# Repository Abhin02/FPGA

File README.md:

# FPGA Interfacing

This project is a set of all the files and documentation of the FPGA project work that was carried out in WEL Laboratory - IIT Bombay during Summer 2016.

## Aim
* To build and program a circuit that uses a CPLD controller to divide computations between two FPGA chips.
* To program Altera CPLD chip using a microcontroller which emulates the Altera USB Blaster. This would allow direct programming from Quartus II without the hassles of external hardware requirements, UrJTAG and the need to create Serial Vector files.

## Circuit Designs

We have added the Eagle files for the Krypton Board, an Altera Max V based development board that was designed earlier by WEL Laboratory. We used this board for testing and building the circuit. The files can be found under [eagle/Krypton/](eagle/Krypton/). There are two eagle files, a daughter card for housing the Max V CPLD IC and a main board for the development board peripherals, such as LEDs and switches.

The board we worked on has been designed under [eagle/main_circuit.sch](eagle/main_circuit.sch) and [eagle/main_circuit.sch](eagle/main_circuit.sch)

A detailed documentation of the project can be found in [report.pdf](report.pdf)

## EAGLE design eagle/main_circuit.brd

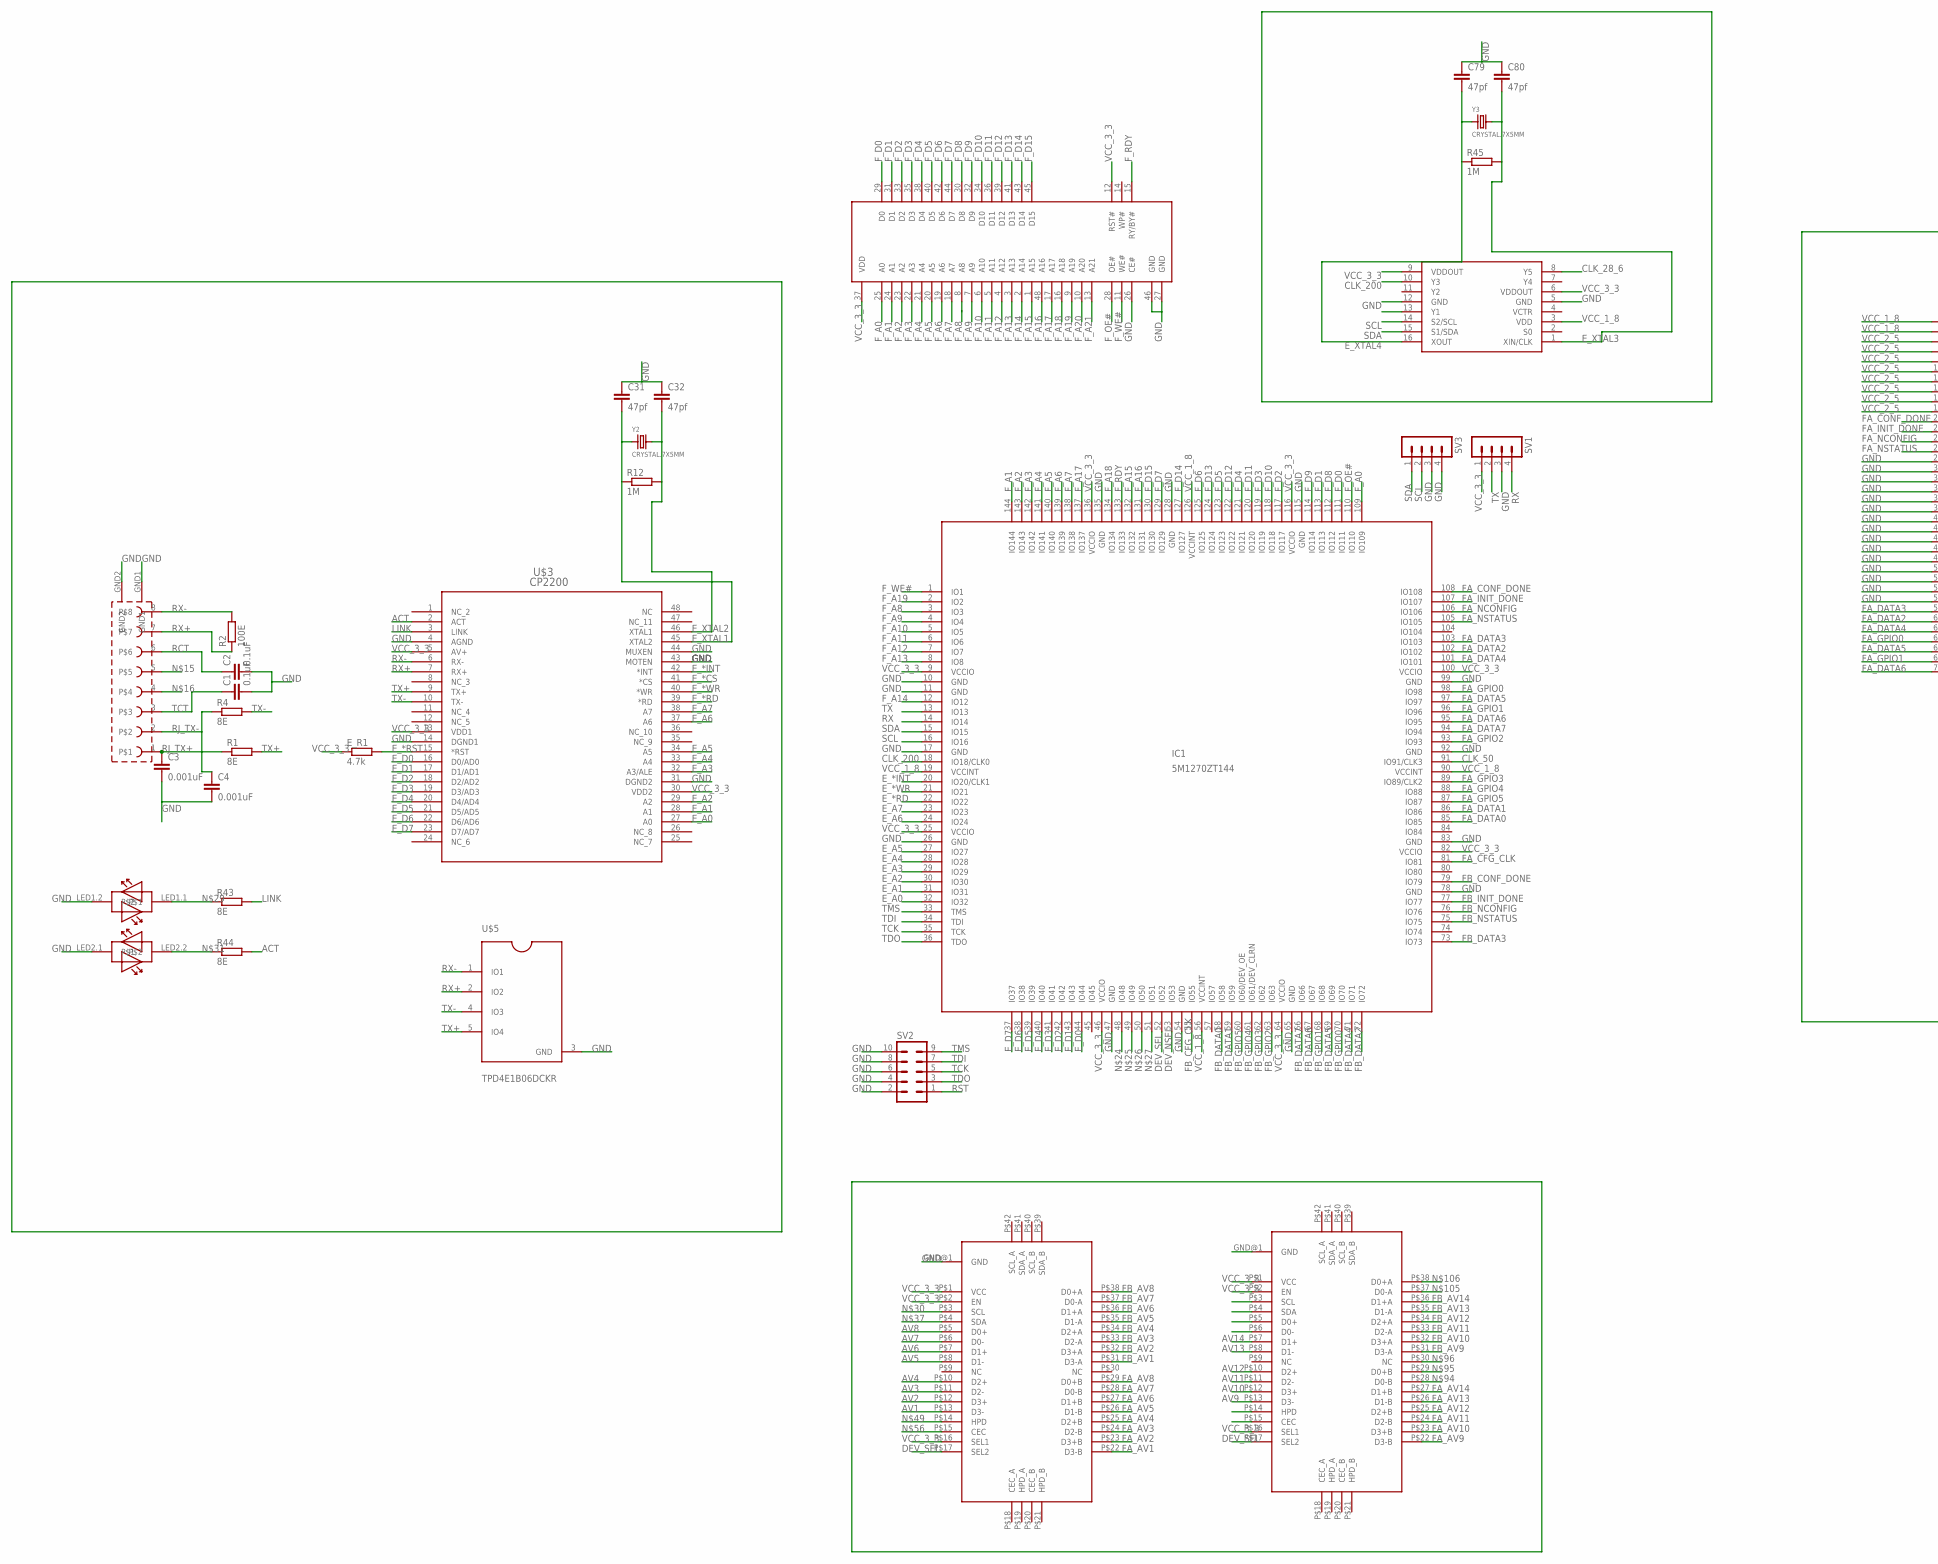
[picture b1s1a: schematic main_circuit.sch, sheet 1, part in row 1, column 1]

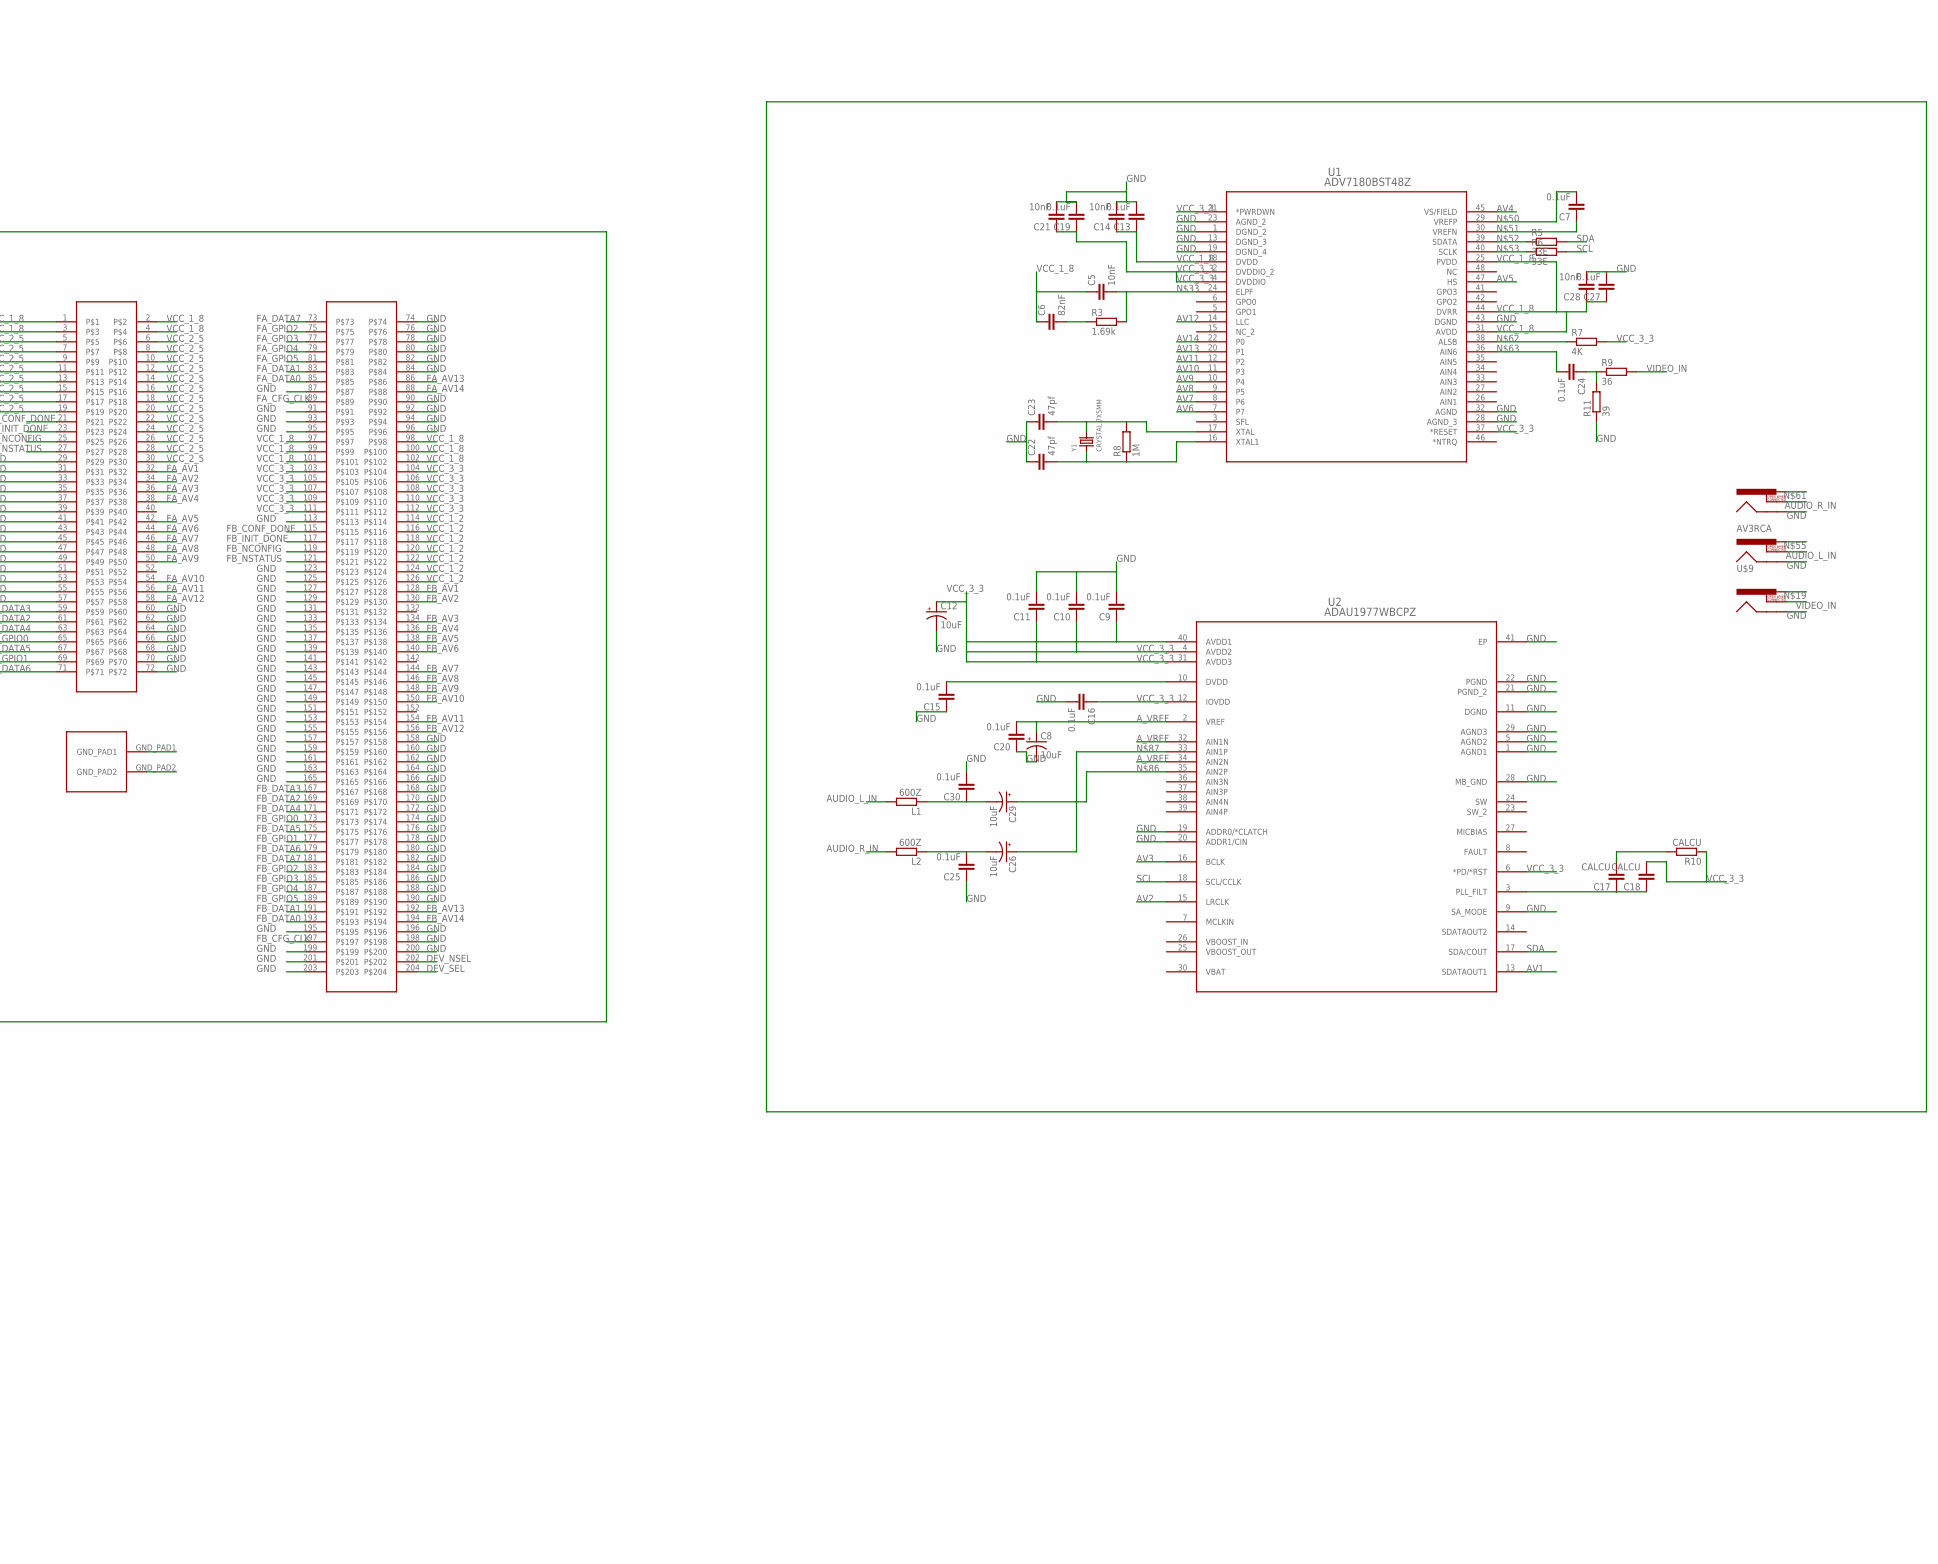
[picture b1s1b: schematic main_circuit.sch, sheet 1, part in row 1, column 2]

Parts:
C1, C2: 0.1uF; C0402
C3, C4: 0.001uF; C0402
C5, C14, C21, C28: 10nF; C0603
C6: 82nF; C0603
C7, C9, C10, C11, C13, C15, C16, C19, C20, C24, C25, C27, C30: 0.1uF; C0603
C8, C12, C26, C29: 10uF; E2,5-6E
C17, C18: CALCU; C0603
C22, C23, C31, C32, C79, C80: 47pf; C0603
E_R1: 4.7k; R0603
GND: TS3DV642; R-PWQFN-N42
IC1: 5M1270ZT144; TQFP144
L1, L2: 600Z; R0603
R1, R4, R43, R44: 8E; R0402
R2: 100E; R0402
R3: 1.69k; R0603
R5, R6: 33E; R0603
R7: 4K; R0603
R8, R12, R45: 1M; R0603
R9: 36; R0603
R10: CALCU; R0603
R11: 39; R0603
SV1, SV3: MA04-1
SV2: MA05-2
U1: ADV7180BST48Z; ST_48
U2: ADAU1977WBCPZ; CP_40_14
U$1: SST39VF64; TSOP48
U$2: CDCE925; R-PDSO-G16
U$3: CP2200; QFP48-7X7-0P5MM
U$4: SODIMM; SODIMM_DDR3_CONN
U$5: TPD4E1B06DCKR; SC70-6
U$6: MAGJACK
U$8: TS3DV642; R-PWQFN-N42
U$9: AV3RCA
Y1, Y2, Y3: CRYSTAL.7X5MM; 7X5MM

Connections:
ACT: R44.2, U$3.2 (ACT)
AUDIO_L_IN: L1.2, U$9.SWITCH
AUDIO_R_IN: L2.2, U$9.SWITCH1
AV1: GND.P$13 (D3-), U2.13 (SDATAOUT1)
AV2: GND.P$12 (D3+), U2.15 (LRCLK)
AV3: GND.P$11 (D2-), U2.16 (BCLK)
AV4: GND.P$10 (D2+), U1.45 (VS/FIELD)
AV5: GND.P$8 (D1-), U1.47 (HS)
AV6: GND.P$7 (D1+), U1.7
AV7: GND.P$6 (D0-), U1.8 (P6)
AV8: GND.P$5 (D0+), U1.9 (P5)
AV9: U1.10 (P4), U$8.P$13 (D3-)
AV10: U1.11 (P3), U$8.P$12 (D3+)
AV11: U1.12 (P2), U$8.P$11 (D2-)
AV12: U1.14 (LLC), U$8.P$10 (D2+)
AV13: U1.20 (P1), U$8.P$8 (D1-)
AV14: U1.22 (P0), U$8.P$7 (D1+)
A_VREF: C8.+, C20.2, U2.2 (VREF), U2.32 (AIN1N), U2.34 (AIN2N)
CLK_28_6: U$2.8 (Y5)
CLK_50: IC1.91 (IO91/CLK3), U$2.13 (Y1)
CLK_200: IC1.18 (IO18/CLK0), U$2.10 (Y3)
DEV_NSEL: IC1.53 (IO53), U$4.202
DEV_SEL: GND.P$17 (SEL2), IC1.52 (IO52), U$4.204, U$8.P$17 (SEL2)
E_*CS: U$3.41 (*CS)
E_*INT: IC1.20 (IO20/CLK1), U$3.42 (*INT)
E_*RD: IC1.22 (IO22), U$3.39 (*RD)
E_*RST: E_R1.2, U$3.15 (*RST)
E_*WR: IC1.21 (IO21), U$3.40 (*WR)
E_A0: IC1.32 (IO32), U$3.27 (A0)
E_A1: IC1.31 (IO31), U$3.28 (A1)
E_A2: IC1.30 (IO30), U$3.29 (A2)
E_A3: IC1.29 (IO29), U$3.32 (A3/ALE)
E_A4: IC1.28 (IO28), U$3.33 (A4)
E_A5: IC1.27 (IO27), U$3.34 (A5)
E_A6: IC1.24 (IO24), U$3.37 (A6)
E_A7: IC1.23 (IO23), U$3.38 (A7)
E_D0: IC1.44 (IO44), U$3.16 (D0/AD0)
E_D1: IC1.43 (IO43), U$3.17 (D1/AD1)
E_D2: IC1.42 (IO42), U$3.18 (D2/AD2)
E_D3: IC1.41 (IO41), U$3.19 (D3/AD3)
E_D4: IC1.40 (IO40), U$3.20 (D4/AD4)
E_D5: IC1.39 (IO39), U$3.21 (D5/AD5)
E_D6: IC1.38 (IO38), U$3.22 (D6/AD6)
E_D7: IC1.37 (IO37), U$3.23 (D7/AD7)
E_XTAL1: C31.2, R12.1, U$3.45 (XTAL2), Y2.1
E_XTAL2: C32.2, R12.2, U$3.46 (XTAL1), Y2.3 (2)
E_XTAL3: C80.2, R45.2, U$2.1 (XIN/CLK), Y3.3 (2)
E_XTAL4: C79.2, R45.1, U$2.16 (XOUT), Y3.1
FA_AV1: GND.P$22 (D3-B), U$4.32
FA_AV2: GND.P$23 (D3+B), U$4.34
FA_AV3: GND.P$24 (D2-B), U$4.36
FA_AV4: GND.P$25 (D2+B), U$4.38
FA_AV5: GND.P$26 (D1-B), U$4.42
FA_AV6: GND.P$27 (D1+B), U$4.44
FA_AV7: GND.P$28 (D0-B), U$4.46
FA_AV8: GND.P$29 (D0+B), U$4.48
FA_AV9: U$4.50, U$8.P$22 (D3-B)
FA_AV10: U$4.54, U$8.P$23 (D3+B)
FA_AV11: U$4.56, U$8.P$24 (D2-B)
FA_AV12: U$4.58, U$8.P$25 (D2+B)
FA_AV13: U$4.86, U$8.P$26 (D1-B)
FA_AV14: U$4.88, U$8.P$27 (D1+B)
FA_CFG_CLK: IC1.81 (IO81), U$4.89
FA_CONF_DONE: IC1.108 (IO108), U$4.21
FA_DATA0: IC1.85 (IO85), U$4.85
FA_DATA1: IC1.86 (IO86), U$4.83
FA_DATA2: IC1.102 (IO102), U$4.61
FA_DATA3: IC1.103 (IO103), U$4.59
FA_DATA4: IC1.101 (IO101), U$4.63
FA_DATA5: IC1.97 (IO97), U$4.67
FA_DATA6: IC1.95 (IO95), U$4.71
FA_DATA7: IC1.94 (IO94), U$4.73
FA_GPIO0: IC1.98 (IO98), U$4.65
FA_GPIO1: IC1.96 (IO96), U$4.69
FA_GPIO2: IC1.93 (IO93), U$4.75
FA_GPIO3: IC1.89 (IO89/CLK2), U$4.77
FA_GPIO4: IC1.88 (IO88), U$4.79
FA_GPIO5: IC1.87 (IO87), U$4.81
FA_INIT_DONE: IC1.107 (IO107), U$4.23
FA_NCONFIG: IC1.106 (IO106), U$4.25
FA_NSTATUS: IC1.105 (IO105), U$4.27
FB_AV1: GND.P$31 (D3-A), U$4.128
FB_AV2: GND.P$32 (D3+A), U$4.130
FB_AV3: GND.P$33 (D2-A), U$4.134
FB_AV4: GND.P$34 (D2+A), U$4.136
FB_AV5: GND.P$35 (D1-A), U$4.138
FB_AV6: GND.P$36 (D1+A), U$4.140
FB_AV7: GND.P$37 (D0-A), U$4.144
FB_AV8: GND.P$38 (D0+A), U$4.146
FB_AV9: U$4.148, U$8.P$31 (D3-A)
FB_AV10: U$4.150, U$8.P$32 (D3+A)
FB_AV11: U$4.154, U$8.P$33 (D2-A)
FB_AV12: U$4.156, U$8.P$34 (D2+A)
FB_AV13: U$4.192, U$8.P$35 (D1-A)
FB_AV14: U$4.194, U$8.P$36 (D1+A)
FB_CFG_CLK: IC1.55 (IO55), U$4.197
FB_CONF_DONE: IC1.79 (IO79), U$4.115
FB_DATA0: IC1.58 (IO58), U$4.193
FB_DATA1: IC1.59 (IO59), U$4.191
FB_DATA2: IC1.72 (IO72), U$4.169
FB_DATA3: IC1.73 (IO73), U$4.167
FB_DATA4: IC1.71 (IO71), U$4.171
FB_DATA5: IC1.69 (IO69), U$4.175
FB_DATA6: IC1.67 (IO67), U$4.179
FB_DATA7: IC1.66 (IO66), U$4.181
FB_GPIO0: IC1.70 (IO70), U$4.173
FB_GPIO1: IC1.68 (IO68), U$4.177
FB_GPIO2: IC1.63 (IO63), U$4.183
FB_GPIO3: IC1.62 (IO62), U$4.185
FB_GPIO4: IC1.61 (IO61/DEV_CLRN), U$4.187
FB_GPIO5: IC1.60 (IO60/DEV_OE), U$4.189
FB_INIT_DONE: IC1.77 (IO77), U$4.117
FB_NCONFIG: IC1.76 (IO76), U$4.119
FB_NSTATUS: IC1.75 (IO75), U$4.121
F_A0: IC1.109 (IO109), U$1.25 (A0)
F_A1: IC1.144 (IO144), U$1.24 (A1)
F_A2: IC1.143 (IO143), U$1.23 (A2)
F_A3: IC1.142 (IO142), U$1.22 (A3)
F_A4: IC1.141 (IO141), U$1.21 (A4)
F_A5: IC1.140 (IO140), U$1.20 (A5)
F_A6: IC1.139 (IO139), U$1.19 (A6)
F_A7: IC1.138 (IO138), U$1.18 (A7)
F_A8: IC1.3 (IO3), U$1.8 (A8)
F_A9: IC1.4 (IO4), U$1.7 (A9)
F_A10: IC1.5 (IO5), U$1.6 (A10)
F_A11: IC1.6 (IO6), U$1.5 (A11)
F_A12: IC1.7 (IO7), U$1.4 (A12)
F_A13: IC1.8 (IO8), U$1.3 (A13)
F_A14: IC1.12 (IO12), U$1.2 (A14)
F_A15: IC1.132 (IO132), U$1.1 (A15)
F_A16: IC1.131 (IO131), U$1.48 (A16)
F_A17: IC1.137 (IO137), U$1.17 (A17)
F_A18: IC1.134 (IO134), U$1.16 (A18)
F_A19: IC1.2 (IO2), U$1.9 (A19)
F_A20: U$1.10 (A20)
F_A21: U$1.13 (A21)
F_D0: IC1.111 (IO111), U$1.29 (D0)
F_D1: IC1.113 (IO113), U$1.31 (D1)
F_D2: IC1.117 (IO117), U$1.33 (D2)
F_D3: IC1.119 (IO119), U$1.35 (D3)
F_D4: IC1.121 (IO121), U$1.38 (D4)
F_D5: IC1.123 (IO123), U$1.40 (D5)
F_D6: IC1.125 (IO125), U$1.42 (D6)
F_D7: IC1.129 (IO129), U$1.44 (D7)
F_D8: IC1.112 (IO112), U$1.30 (D8)
F_D9: IC1.114 (IO114), U$1.32 (D9)
F_D10: IC1.118 (IO118), U$1.34 (D10)
F_D11: IC1.120 (IO120), U$1.36 (D11)
F_D12: IC1.122 (IO122), U$1.39 (D12)
F_D13: IC1.124 (IO124), U$1.41 (D13)
F_D14: IC1.127 (IO127), U$1.43 (D14)
F_D15: IC1.130 (IO130), U$1.45 (D15)
F_OE#: IC1.110 (IO110), U$1.28 (OE#)
F_RDY: IC1.133 (IO133), U$1.15 (RY/BY#)
F_WE#: IC1.1 (IO1), U$1.11 (WE#)
GND: C1.2, C2.2, C3.2, C4.2, C8.-, C9.2, C10.2, C11.2, C12.-, C13.2, C14.2, C15.1, C16.2, C19.2, C20.1, C21.2, C22.1, C23.1, C25.1, C27.2, C28.2, C30.2, C31.1, C32.1, C79.1, C80.1, GND.GND@1 (GND), IC1.10 (GND), IC1.11 (GND), IC1.17 (GND), IC1.26 (GND), IC1.47 (GND), IC1.54 (GND), IC1.65 (GND), IC1.78 (GND), IC1.83 (GND), IC1.92 (GND), IC1.99 (GND), IC1.115 (GND), IC1.128 (GND), IC1.135 (GND), R11.1, SV1.3, SV2.2, SV2.4, SV2.6, SV2.8, SV2.10, SV3.3, SV3.4, U1.1 (DGND_2), U1.13 (DGND_3), U1.19 (DGND_4), U1.23 (AGND_2), U1.28 (AGND_3), U1.32 (AGND), U1.43 (DGND), U2.1 (AGND1), U2.5 (AGND2), U2.9 (SA_MODE), U2.11 (DGND), U2.19 (ADDR0/*CLATCH), U2.20 (ADDR1/CIN), U2.21 (PGND_2), U2.22 (PGND), U2.28 (MB_GND), U2.29 (AGND3), U2.41 (EP), U$1.26 (CE#), U$1.27 (GND), U$1.46 (GND), U$2.5 (GND), U$2.12 (GND), U$3.4 (AGND), U$3.14 (DGND1), U$3.31 (DGND2), U$3.43 (MOTEN), U$3.44 (MUXEN), U$4.29, U$4.31, U$4.33, U$4.35, U$4.37, U$4.39, U$4.41, U$4.43, U$4.45, U$4.47, U$4.49, U$4.51, U$4.53, U$4.55, U$4.57, U$4.60, U$4.62, U$4.64, U$4.66, U$4.68, U$4.70, U$4.72, U$4.74, U$4.76, U$4.78, U$4.80, U$4.82, U$4.84, U$4.87, U$4.90, U$4.91, U$4.92, U$4.93, U$4.94, U$4.95, U$4.96, U$4.113, U$4.123, U$4.125, U$4.127, U$4.129, U$4.131, U$4.133, U$4.135, U$4.137, U$4.139, U$4.141, U$4.143, U$4.145, U$4.147, U$4.149, U$4.151, U$4.153, U$4.155, U$4.157, U$4.158, U$4.159, U$4.160, U$4.161, U$4.162, U$4.163, U$4.164, U$4.165, U$4.166, U$4.168, U$4.170, U$4.172, U$4.174, U$4.176, U$4.178, U$4.180, U$4.182, U$4.184, U$4.186, U$4.188, U$4.190, U$4.195, U$4.196, U$4.198, U$4.199, U$4.200, U$4.201, U$4.203, U$4.GND_PAD1, U$4.GND_PAD2, U$5.3 (GND), U$6.GND1, U$6.GND2, U$6.LED1.2, U$6.LED2.1, U$8.GND@1 (GND), U$9.SHELL, U$9.SHELL1, U$9.SHELL2; also elsewhere on the board
IO104: IC1.104 (IO104)
LINK: R43.2, U$3.3 (LINK)
unnamed: C29.-, C30.1, L1.1
unnamed: C6.2, R3.1
unnamed: C15.2, U2.10 (DVDD)
unnamed: C25.2, C26.-, L2.1
unnamed: C24.1, R9.1, R11.2
unnamed: R43.1, U$6.LED1.1
unnamed: R44.1, U$6.LED2.2
unnamed: C5.2, R3.2, U1.24 (ELPF)
unnamed: C17.2, R10.2
unnamed: C17.1, C18.1, U2.3 (PLL_FILT)
unnamed: C23.2, R8.2, U1.17 (XTAL), Y1.3 (2)
unnamed: C22.2, R8.1, U1.16 (XTAL1), Y1.1
unnamed: C7.2, U1.29 (VREFP)
unnamed: C7.1, U1.30 (VREFN)
unnamed: R5.1, U1.39 (SDATA)
unnamed: R6.1, U1.40 (SCLK)
unnamed: R7.1, U1.38 (ALSB)
unnamed: C24.2, U1.36 (AIN6)
unnamed: C29.+, U2.35 (AIN2P)
unnamed: C26.+, U2.33 (AIN1P)
RCT: C2.1, U$6.6
RJ_TX+: C3.1, R1.1, U$6.1
RJ_TX-: C4.1, R4.1, U$6.2
RST: SV2.1
RX: IC1.14 (IO14), SV1.4
RX+: R2.1, U$3.7 (RX+), U$5.2 (IO2), U$6.7
RX-: R2.2, U$3.6 (RX-), U$5.1 (IO1), U$6.8
SCL: IC1.16 (IO16), R6.2, SV3.2, U2.18 (SCL/CCLK), U$2.14 (S2/SCL); also elsewhere on the board
SDA: IC1.15 (IO15), R5.2, SV3.1, U2.17 (SDA/COUT), U$2.15 (S1/SDA); also elsewhere on the board
TCK: IC1.35 (TCK), SV2.5; also elsewhere on the board
TCT: C1.1, U$6.3
TDI: IC1.34 (TDI), SV2.7; also elsewhere on the board
TDO: IC1.36 (TDO), SV2.3; also elsewhere on the board
TMS: IC1.33 (TMS), SV2.9; also elsewhere on the board
TX: IC1.13 (IO13), SV1.2
TX+: R1.2, U$3.9 (TX+), U$5.5 (IO4)
TX-: R4.2, U$3.10 (TX-), U$5.4 (IO3)
VCC_1_2: U$4.114, U$4.116, U$4.118, U$4.120, U$4.122, U$4.124, U$4.126; also elsewhere on the board
VCC_1_8: C5.1, C6.1, C13.1, C14.1, C27.1, C28.1, IC1.19 (VCCINT), IC1.56 (VCCINT), IC1.90 (VCCINT), IC1.126 (VCCINT), U1.18 (DVDD), U1.25 (PVDD), U1.31 (AVDD), U1.44 (DVRR), U$2.3 (VDD), U$4.1, U$4.2, U$4.3, U$4.4, U$4.97, U$4.98, U$4.99, U$4.100, U$4.101, U$4.102; also elsewhere on the board
VCC_2_5: U$4.5, U$4.6, U$4.7, U$4.8, U$4.9, U$4.10, U$4.11, U$4.12, U$4.13, U$4.14, U$4.15, U$4.16, U$4.17, U$4.18, U$4.19, U$4.20, U$4.22, U$4.24, U$4.26, U$4.28, U$4.30; also elsewhere on the board
VCC_3_3: C9.1, C10.1, C11.1, C12.+, C16.1, C18.2, C19.1, C21.1, E_R1.1, GND.P$1 (VCC), GND.P$2 (EN), GND.P$16 (SEL1), IC1.9 (VCCIO), IC1.25 (VCCIO), IC1.46 (VCCIO), IC1.64 (VCCIO), IC1.82 (VCCIO), IC1.100 (VCCIO), IC1.116 (VCCIO), IC1.136 (VCCIO), R7.2, R10.1, SV1.1, U1.2 (DVDDIO_2), U1.4 (DVDDIO), U1.21 (*PWRDWN), U1.37 (*RESET), U2.4 (AVDD2), U2.6 (*PD/*RST), U2.12 (IOVDD), U2.31 (AVDD3), U2.40 (AVDD1), U$1.12 (RST#), U$1.37 (VDD), U$2.6 (VDDOUT), U$2.9 (VDDOUT), U$3.5 (AV+), U$3.13 (VDD1), U$3.30 (VDD2), U$4.103, U$4.104, U$4.105, U$4.106, U$4.107, U$4.108, U$4.109, U$4.110, U$4.111, U$4.112, U$8.P$1 (VCC), U$8.P$2 (EN), U$8.P$16 (SEL1); also elsewhere on the board
VIDEO_IN: R9.2, U$9.SWITCH2

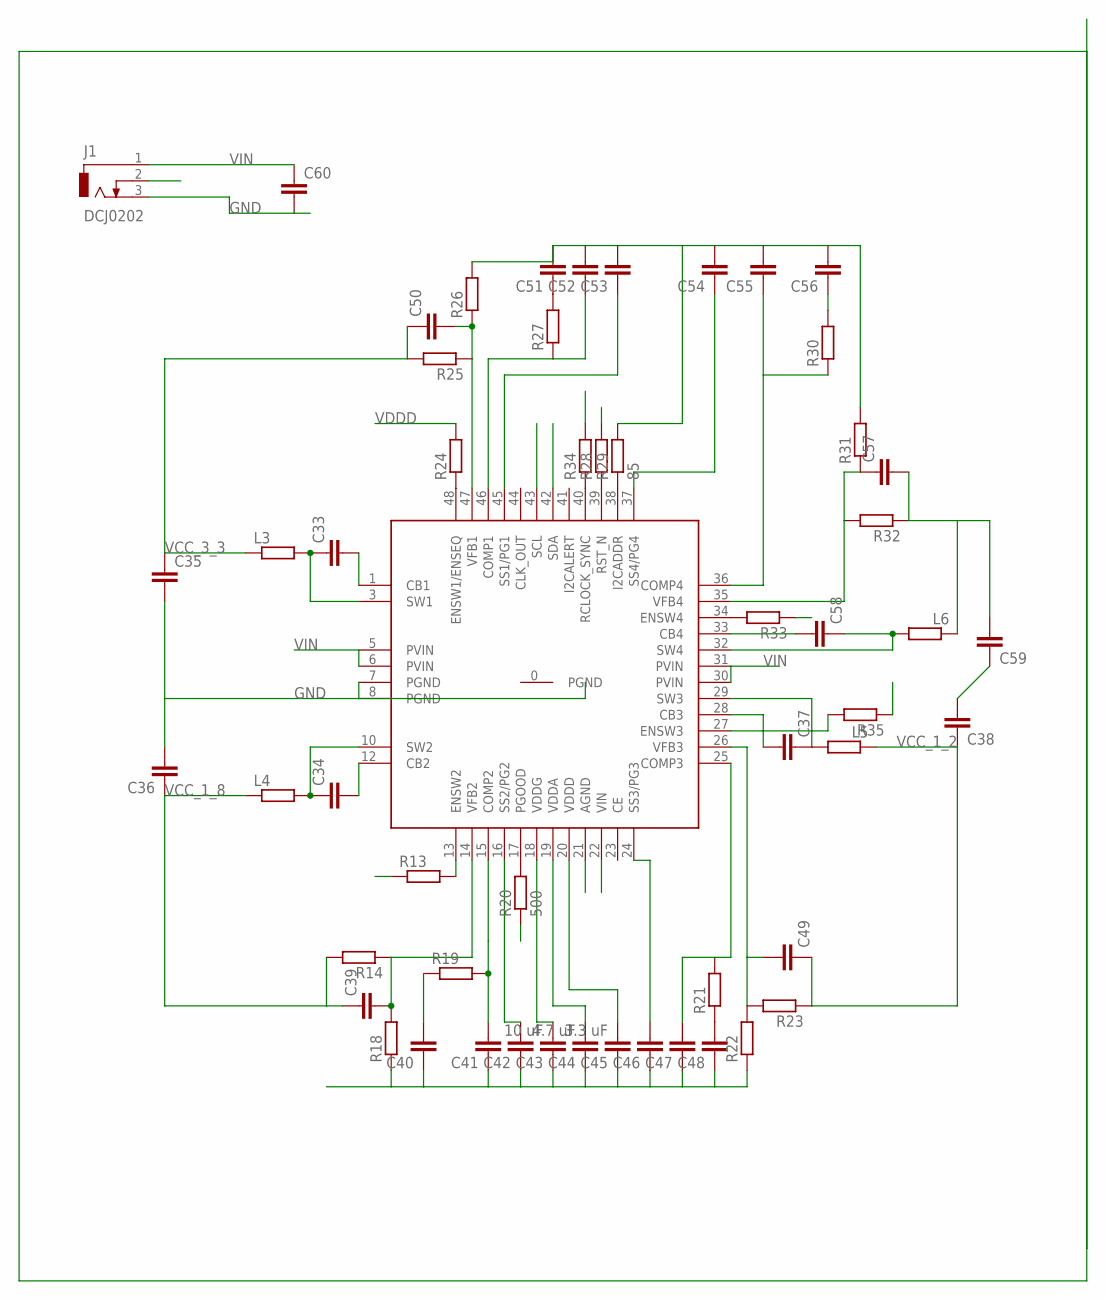
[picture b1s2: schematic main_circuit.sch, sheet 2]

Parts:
C33, C34, C35, C36, C37, C38, C39, C40, C41, C42, C46, C47, C48, C49, C50, C51, C52, C53, C54, C55, C56, C57, C58, C59, C60: CC0603; C0603
C43: 10 uF; C0603
C44: 4.7 uF; C0603
C45: 3.3 uF; C0603
J1: DCJ0202
L3, L4, L5, L6: RR0603; R0603
R13, R14, R18, R19, R21, R22, R23, R24, R25, R26, R27, R28, R30, R31, R32, R33, R34, R35: RR0603; R0603
R20: 500; R0603
R29: 85; R0603
U$10: TPS65400RGZR; VQFN48

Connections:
ENSW3: R35.2, U$10.27 (ENSW3)
ENSW4: R33.2, U$10.34 (ENSW4)
GND: C35.2, C36.2, C38.2, C40.1, C41.1, C42.1, C43.1, C44.1, C45.1, C46.1, C47.1, C48.1, C51.2, C52.2, C53.2, C54.2, C55.2, C56.2, C60.2, J1.3, R18.1, R22.1, R26.2, R29.2, R31.2, R34.2, U$10.7 (PGND), U$10.8 (PGND), U$10.21 (AGND); also elsewhere on the board
unnamed: C33.2, U$10.1 (CB1)
unnamed: C33.1, L3.2, U$10.3 (SW1)
unnamed: C34.1, L4.2, U$10.10 (SW2)
unnamed: C34.2, U$10.12 (CB2)
unnamed: C37.1, L5.2, U$10.29 (SW3)
unnamed: C37.2, U$10.28 (CB3)
unnamed: R13.2, U$10.13 (ENSW2)
unnamed: C39.2, R14.1, R18.2, U$10.14 (VFB2)
unnamed: C40.2, R19.1
unnamed: R20.2, U$10.17 (PGOOD)
unnamed: C41.2, R19.2, U$10.15 (COMP2)
unnamed: C43.2, U$10.18 (VDDG)
unnamed: C44.2, U$10.19 (VDDA)
unnamed: C46.2, U$10.24 (SS3/PG3)
unnamed: C42.2, U$10.16 (SS2/PG2)
unnamed: C48.2, R21.1
unnamed: C49.2, R22.2, R23.2, U$10.26 (VFB3)
unnamed: C47.2, R21.2, U$10.25 (COMP3)
unnamed: R24.1, U$10.48 (ENSW1/ENSEQ)
unnamed: C51.1, R27.2
unnamed: R29.1, U$10.38 (I2CADDR)
unnamed: C57.1, R31.1, R32.2, U$10.35 (VFB4)
unnamed: C58.1, L6.2, U$10.32 (SW4)
unnamed: C50.2, R25.1, R26.1, U$10.47 (VFB1)
unnamed: C56.1, R30.2
unnamed: C52.1, R27.1, U$10.46 (COMP1)
unnamed: C53.1, U$10.45 (SS1/PG1)
unnamed: C54.1, U$10.37 (SS4/PG4)
unnamed: C55.1, R30.1, U$10.36 (COMP4)
unnamed: C58.2, U$10.33 (CB4)
unnamed: R34.1, U$10.40 (RCLOCK_SYNC)
RST_N: R28.1, U$10.39 (RST_N)
SCL: U$10.43 (SCL); also elsewhere on the board
SDA: U$10.42 (SDA); also elsewhere on the board
VCC_1_2: C38.1, C49.1, L5.1, R23.1; also elsewhere on the board
VCC_1_8: C36.1, C39.1, L4.1, R14.2; also elsewhere on the board
VCC_2_5: C57.2, C59.2, L6.1, R32.1; also elsewhere on the board
VCC_3_3: C35.1, C50.1, L3.1, R25.2; also elsewhere on the board
VDDD: C45.2, R13.1, R20.1, R24.2, R28.2, R33.1, R35.1, U$10.20 (VDDD)
VIN: C60.1, J1.1, U$10.5 (PVIN), U$10.6 (PVIN), U$10.22 (VIN), U$10.30 (PVIN), U$10.31 (PVIN)

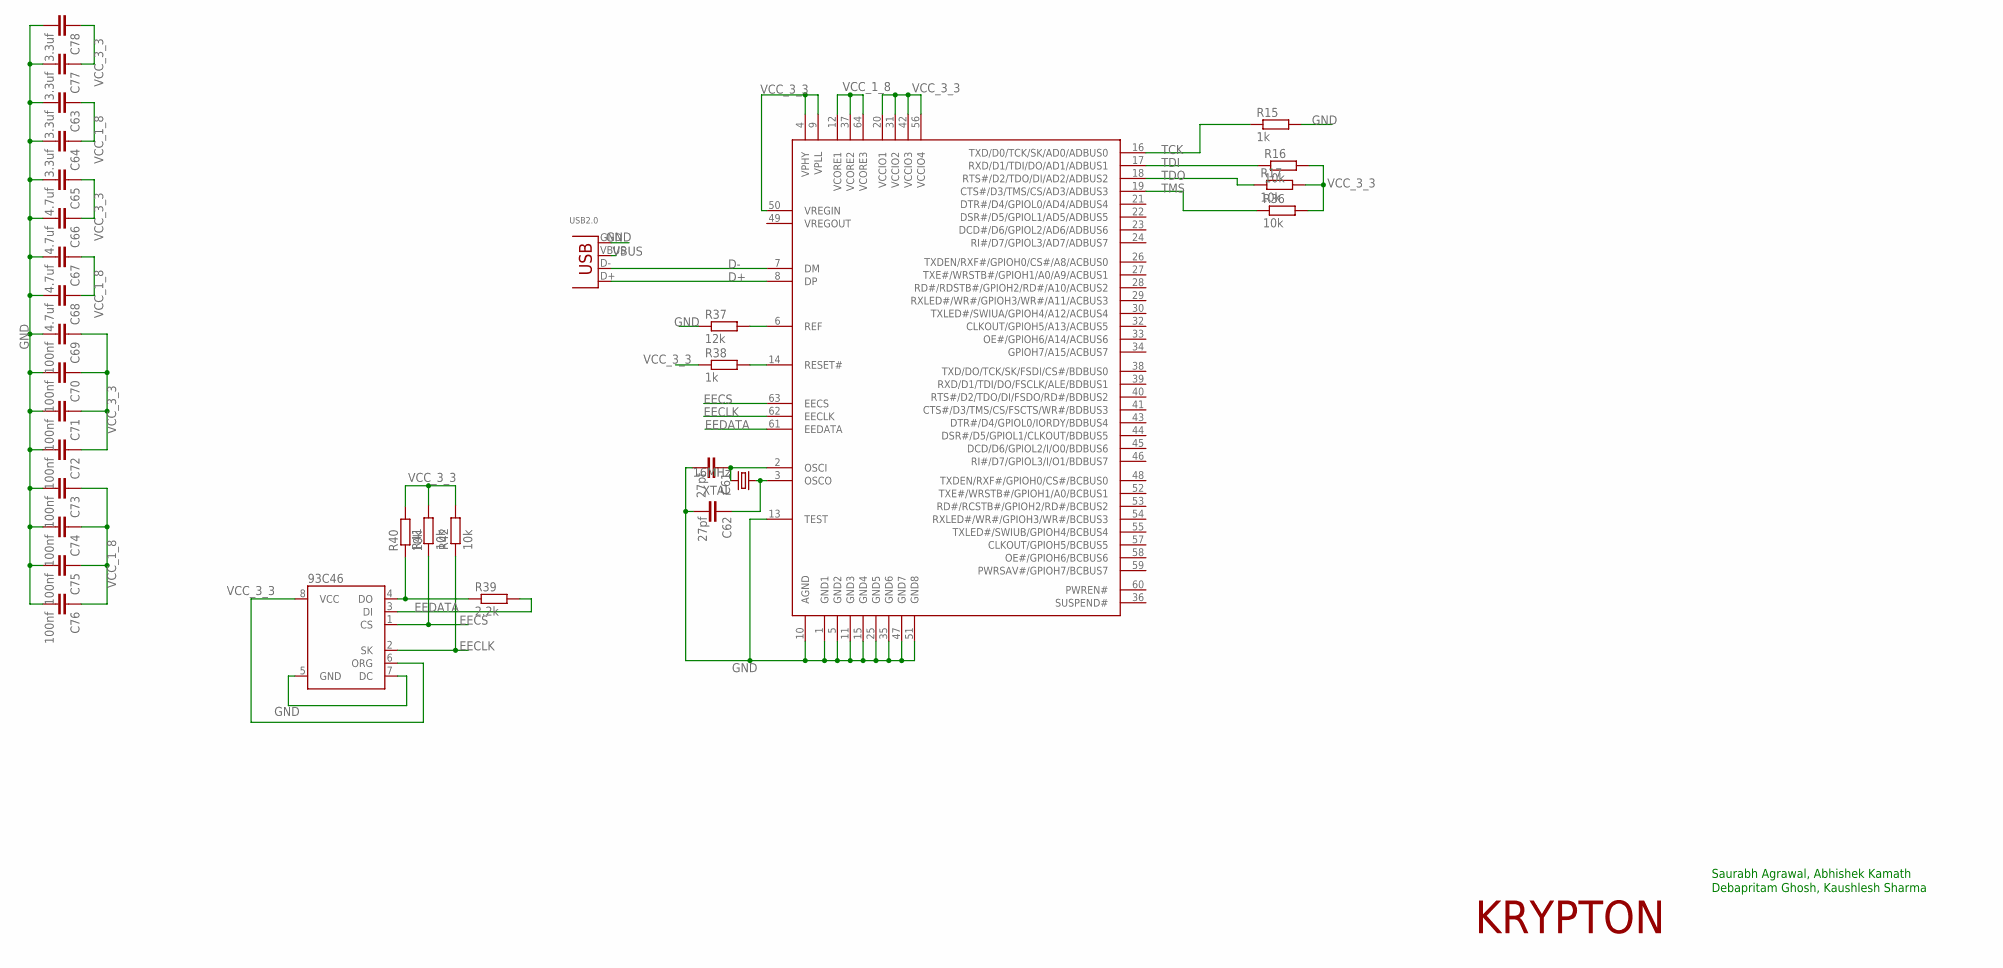
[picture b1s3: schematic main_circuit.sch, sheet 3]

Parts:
93C46: AT93C6; SOIC8
C61, C62: 27pf; C0603
C63, C64, C77, C78: 3.3uf; C0603
C65, C66, C67, C68: 4.7uf; C0603
C69, C70, C71, C72, C73, C74, C75, C76: 100nf; C0603
FT2232H: FT2232H; LQFP_NEW
R15, R38: 1k; R0603
R16, R17, R36, R40, R41, R42: 10k; R0603
R37: 12k; R0603
R39: 2.2k; R0603
USB2.0: USB-B-H
XTAL: 16MHz; HC18U-V

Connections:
D+: FT2232H.8 (DP), USB2.0.D+
D-: FT2232H.7 (DM), USB2.0.D-
EECLK: 93C46.2 (SK), FT2232H.62 (EECLK), R42.1
EECS: 93C46.1 (CS), FT2232H.63 (EECS), R41.1
EEDATA: 93C46.3 (DI), FT2232H.61 (EEDATA), R39.2
GND: 93C46.5 (GND), 93C46.7 (DC), C61.2, C62.2, C63.2, C64.2, C65.2, C66.2, C67.2, C68.2, C69.2, C70.2, C71.2, C72.2, C73.2, C74.2, C75.2, C76.2, C77.2, C78.2, FT2232H.1 (GND1), FT2232H.5 (GND2), FT2232H.10 (AGND), FT2232H.11 (GND3), FT2232H.13 (TEST), FT2232H.15 (GND4), FT2232H.25 (GND5), FT2232H.35 (GND6), FT2232H.47 (GND7), FT2232H.51 (GND8), R15.2, R37.1, USB2.0.GND; also elsewhere on the board
unnamed: FT2232H.6 (REF), R37.2
unnamed: FT2232H.14 (RESET#), R38.2
unnamed: 93C46.4 (DO), R39.1, R40.1
OSCI: C61.1, FT2232H.2 (OSCI), XTAL.2
OSCO: C62.1, FT2232H.3 (OSCO), XTAL.1
TCK: FT2232H.16 (TXD/D0/TCK/SK/AD0/ADBUS0), R15.1; also elsewhere on the board
TDI: FT2232H.17 (RXD/D1/TDI/DO/AD1/ADBUS1), R16.1; also elsewhere on the board
TDO: FT2232H.18 (RTS#/D2/TDO/DI/AD2/ADBUS2), R17.1; also elsewhere on the board
TMS: FT2232H.19 (CTS#/D3/TMS/CS/AD3/ADBUS3), R36.1; also elsewhere on the board
VBUS: USB2.0.VBUS
VCC_1_8: C63.1, C64.1, C67.1, C68.1, C73.1, C74.1, C75.1, C76.1, FT2232H.12 (VCORE1), FT2232H.37 (VCORE2), FT2232H.64 (VCORE3); also elsewhere on the board
VCC_3_3: 93C46.6 (ORG), 93C46.8 (VCC), C65.1, C66.1, C69.1, C70.1, C71.1, C72.1, C77.1, C78.1, FT2232H.4 (VPHY), FT2232H.9 (VPLL), FT2232H.20 (VCCIO1), FT2232H.31 (VCCIO2), FT2232H.42 (VCCIO3), FT2232H.50 (VREGIN), FT2232H.56 (VCCIO4), R16.2, R17.2, R36.2, R38.1, R40.2, R41.2, R42.2; also elsewhere on the board

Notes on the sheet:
Saurabh Agrawal, Abhishek Kamath
Debapritam Ghosh, Kaushlesh Sharma
KRYPTON

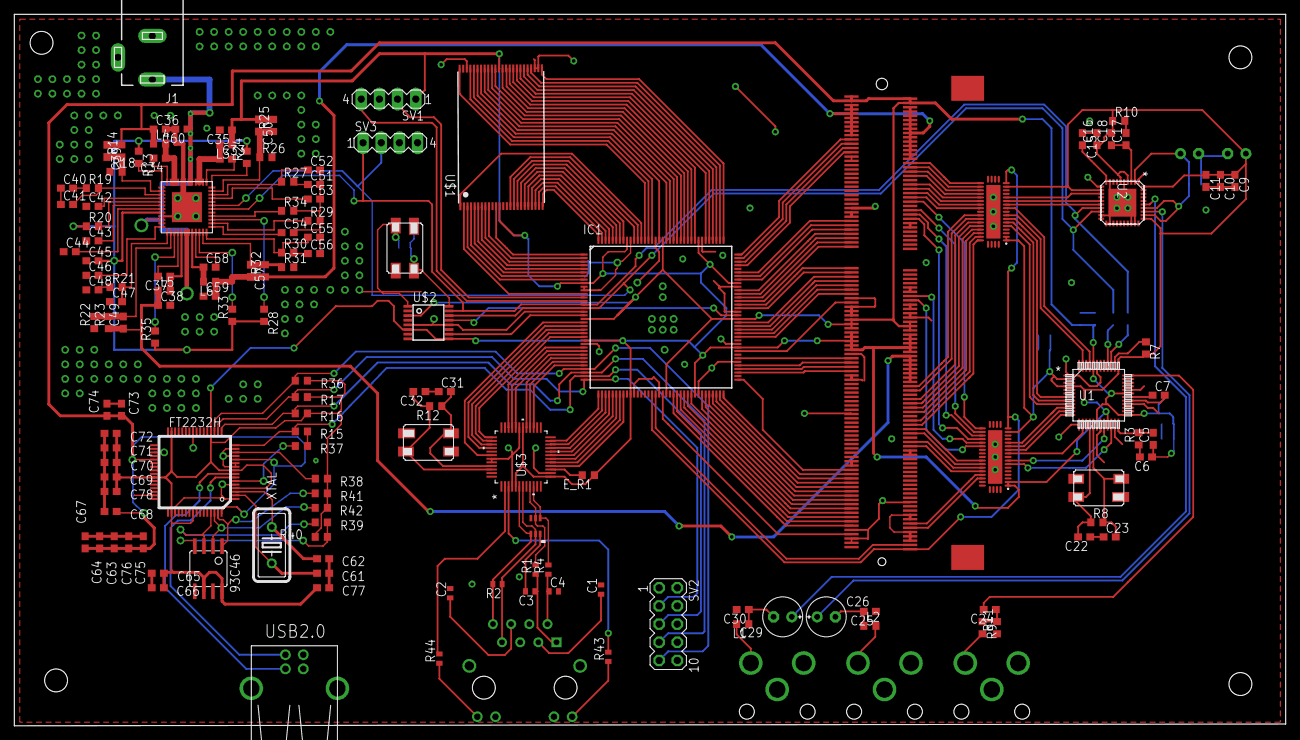
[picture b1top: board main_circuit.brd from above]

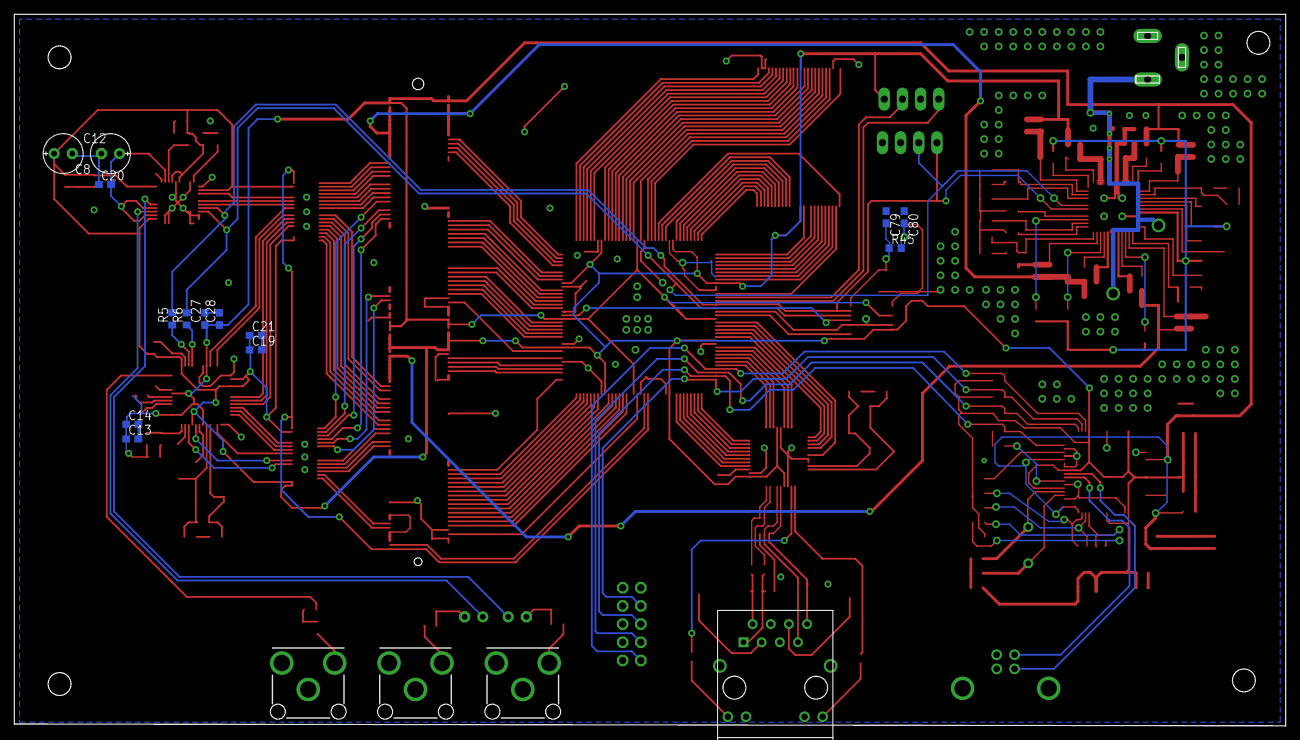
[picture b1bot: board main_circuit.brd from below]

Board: 2 copper layers, 177.8 x 99.5 mm, 156 parts (16 on the bottom side), 240 nets.

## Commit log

2016-07-14 Adding old documentation.
2016-07-14 Adding tex file.
2016-07-14 Adding Arduino codes
2016-07-14 1st edited tex file
2016-07-14 Structuring
2016-07-14 Adding readme file
2016-07-14 Removing temporary files and adding a .gitignore file
2016-07-14 Changing file and folder names
2016-07-14 Updating documentation, changing a few files
2016-07-14 Readme update
2016-07-15 Adding a local leftover documentation

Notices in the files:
parts and their libraries:
SparkFun-Connectors: Licensing: CC v3.0 Share-Alike You are welcome to use this library for commercial purposes.
